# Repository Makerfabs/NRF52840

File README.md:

# MakePython nRF52840

```c++
/*
Version:		V2.0
Author:			UNKOWN
Create Date:	UNKOWN
Note:
	2020/7/24	v2.0: Rebuid readme,add pic. By Vincent
*/
```

[toc]

# Introduce

Python is one of the most widely used, simple and easy-to-learn programming languages around. CircuitPython is a lean implementation of the Python 3 programming language that has been pared down to run efficiently on microcontrollers.
MakePython nRF52840 is a powerful, generic BLE MCU module target to CircuitPython/MicroPython learners & developers. It is true “breadboard compatible”, with the very detailed pins explanation, it is easy to learn& use. The nRF52840 is ready to take advantage of the considerable performance improvements for Bluetooth Low Energy (LE) with the arrival of the Bluetooth 5 specification. Of greatest importance is the support for longer range (up to x4 compared to Bluetooth 4.x) and doubling of on-air data rate, up to 2 Mbs from 1 Mbs in Bluetooth 4.x
The MakePython nRF52840 leads out all pins of Nordic nRF52840, is programmed with CircuitPython by default, users can begin the CircuitPython developing as getting then on hand. It is also compatible with the Arduino making it easy to get started if the correct bootloader downloaded. There also the Makerfabs MakePython ESP8266, MakePython ESP32 and so on.

- You can get one from: [MakePython_nRF52840](https://www.makerfabs.com/makepython-nrf52840.html)

- Hardware and detailed instructions please visit Wiki page: [MakePython_nRF52840 Wiki](https://wiki.makerfabs.com/MaESP_nRF52840.html)

# Related Test

Visit the wiki for details.

- Display animation

- bluetooth communication

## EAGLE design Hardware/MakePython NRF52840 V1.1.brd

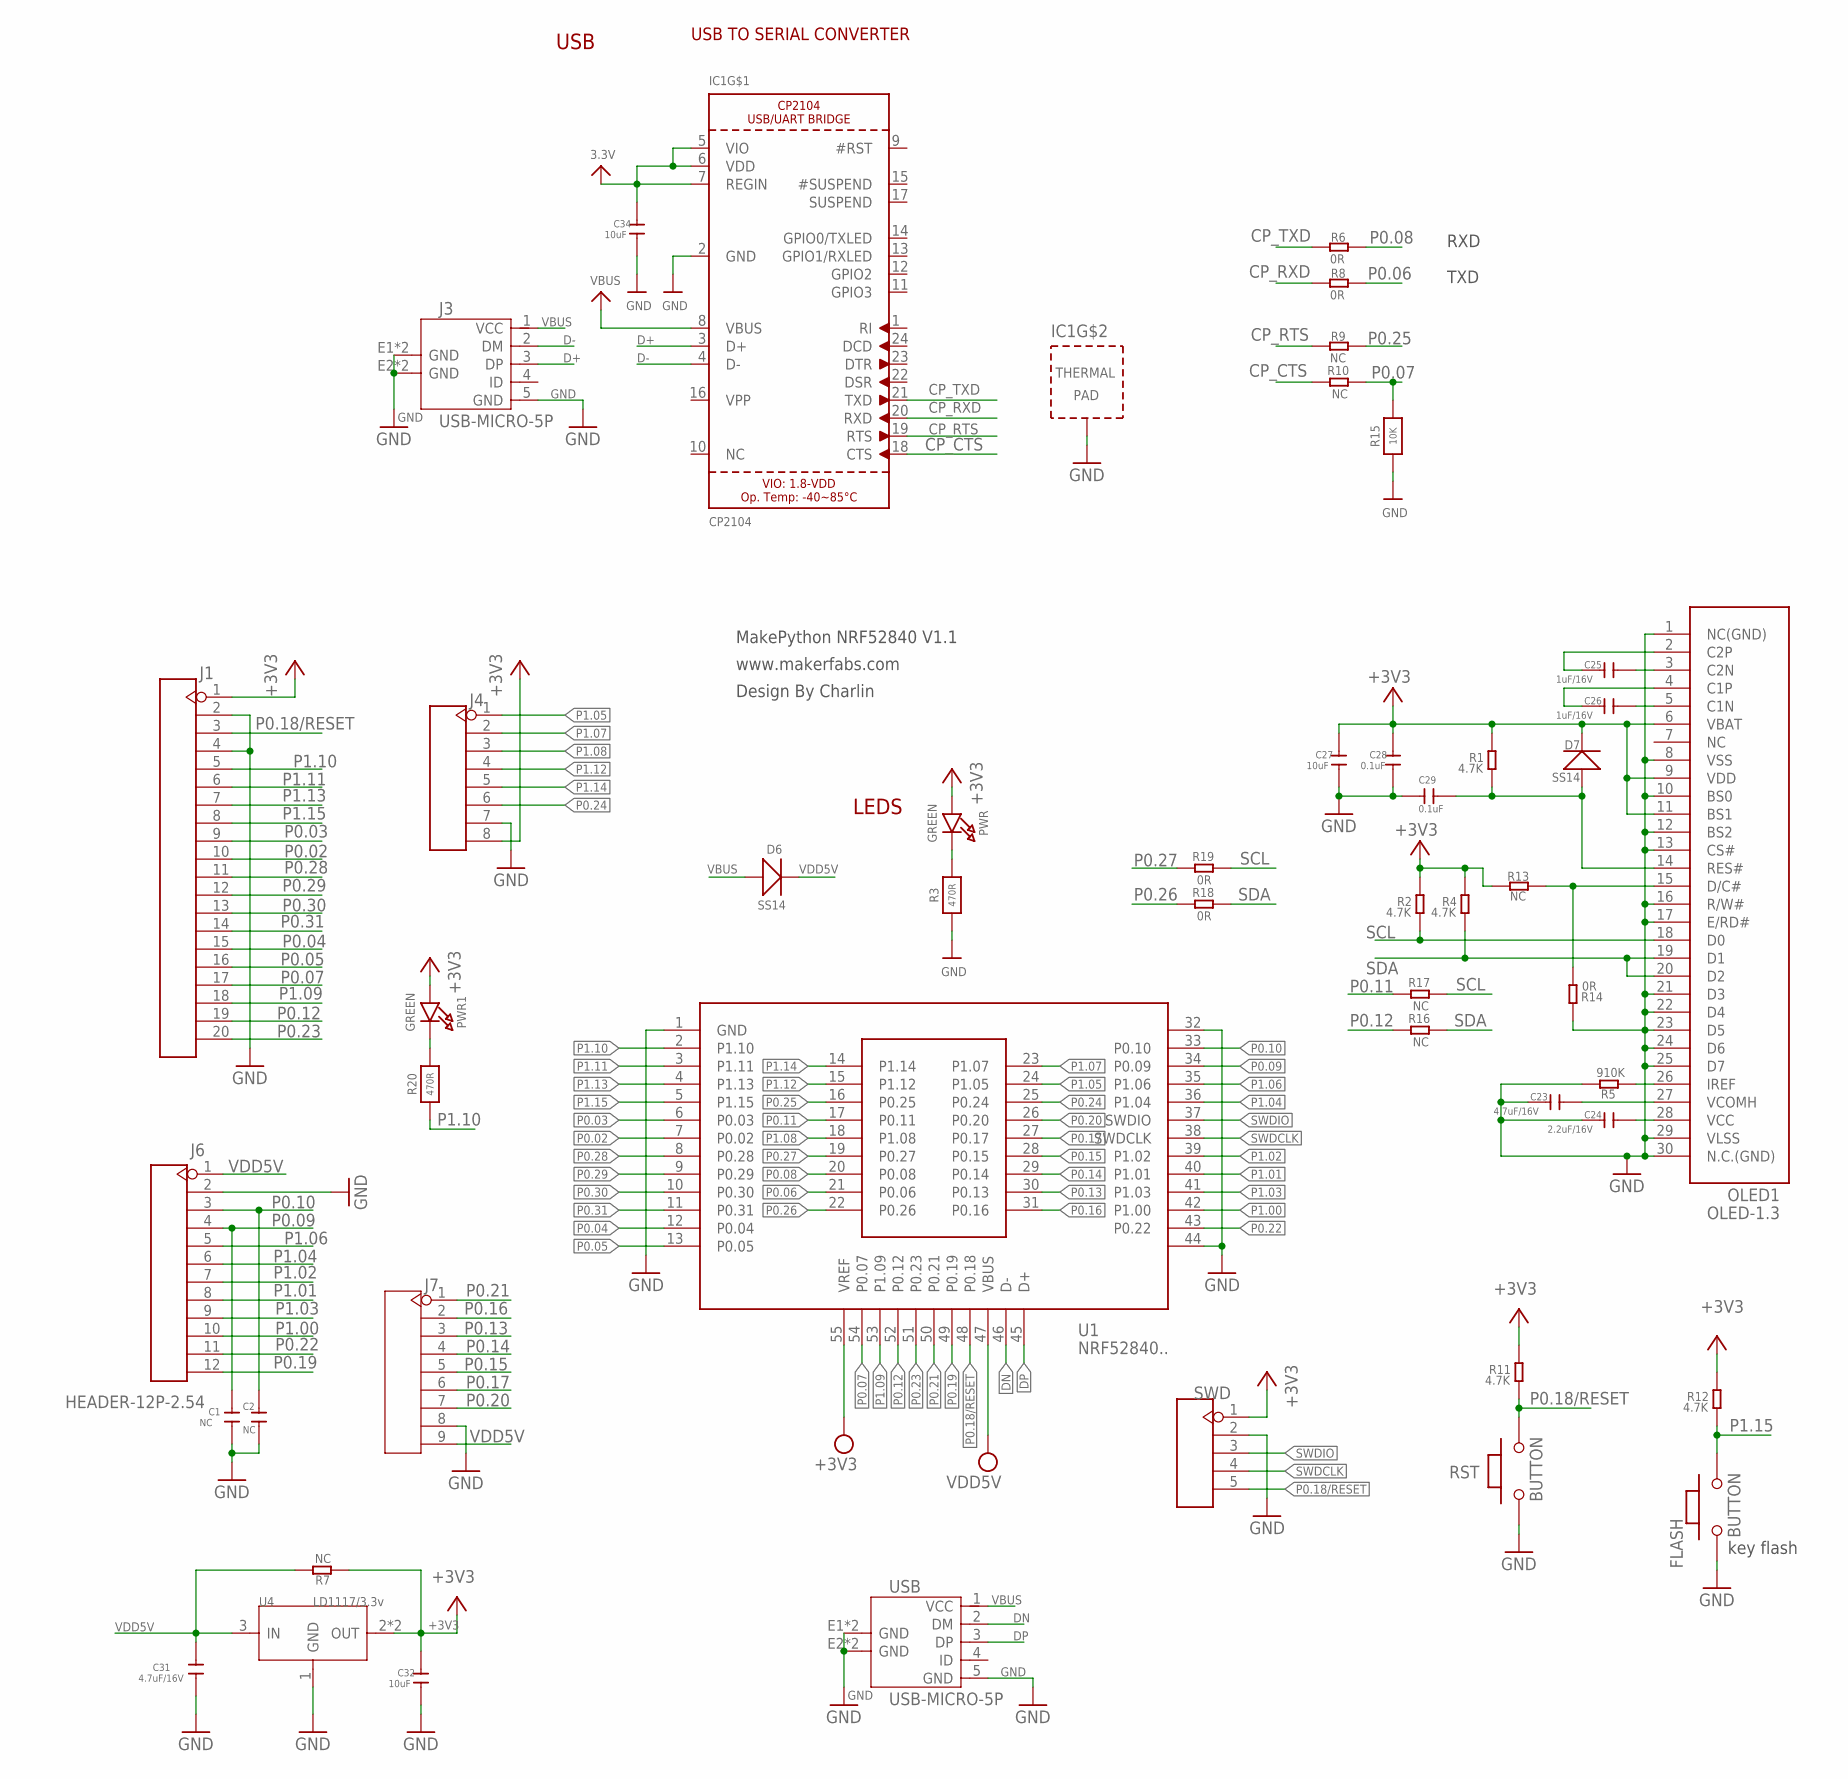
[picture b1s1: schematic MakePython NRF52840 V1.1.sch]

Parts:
C1, C2: NC; C0603
C23, C31: 4.7uF/16V; C0603
C24: 2.2uF/16V; C0603
C25, C26: 1uF/16V; C0603
C27, C32, C34: 10uF; C0603
C28, C29: 0.1uF; C0603
D6, D7: SS14; SOD323
FLASH: BUTTON; 157SW
IC1: CP2104; QFN24_4MM_SMSC
J1: HEADER-20P-2.54; 20P-2.54
J3: USB-MICRO-5P; MICRO-USB-5P
J4: HEADER-8P-2.54; 8P-2.54
J6: HEADER-12P-2.54; 12P-2.54
J7: HEADER-9P-2.54; 9P-2.54
OLED1: OLED-1.3
PWR, PWR1: GREEN; CHIPLED_0805_NOOUTLINE
R1, R2, R4, R11, R12: 4.7K; 0603
R3, R20: 470R; 0603-NO
R5: 910K; 0603
R6, R8, R14, R18, R19: 0R; 0603
R7, R9, R10, R13, R16, R17: NC; 0603
R15: 10K; 0603-NO
RST: BUTTON; 157SW
SWD: HEADER-5P-2.54; 5P-2.54
U1: NRF52840..
U4: LD1117/3.3v; SOT89
USB: USB-MICRO-5P; MICRO-USB-5P

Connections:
+3V3: C27.1, C28.1, C32.1, C34.1, D7.-, IC1.5 (VIO), IC1.6 (VDD), IC1.7 (REGIN), J1.1, J4.8, OLED1.6 (VBAT), OLED1.9 (VDD), OLED1.11 (BS1), PWR.A, PWR1.A, R1.2, R2.2, R4.2, R7.2, R11.2, R12.2, R13.2, SWD.1, U1.55 (VREF), U4.2 (OUT), U4.4 (OUT)
CP_CTS: IC1.18 (CTS), R10.2
CP_RTS: IC1.19 (RTS), R9.2
CP_RXD: IC1.20 (RXD), R8.2
CP_TXD: IC1.21 (TXD), R6.2
D+: IC1.3 (D+), J3.3 (DP)
D-: IC1.4 (D-), J3.2 (DM)
DN: U1.46 (D-), USB.2 (DM)
DP: U1.45 (D+), USB.3 (DP)
GND: C1.2, C2.2, C23.2, C24.2, C27.2, C28.2, C29.1, C31.2, C32.2, C34.2, FLASH.1, IC1.2 (GND), IC1.THERM (TP), J1.2, J1.4, J3.5 (GND), J3.E1 (GND), J3.E2 (GND), J3.P1 (GND), J3.P2 (GND), J4.7, J6.2, J7.8, OLED1.1 (NC(GND)), OLED1.8 (VSS), OLED1.10 (BS0), OLED1.12 (BS2), OLED1.13 (CS#), OLED1.16 (R/W#), OLED1.17 (E/RD#), OLED1.21 (D3), OLED1.22 (D4), OLED1.23 (D5), OLED1.24 (D6), OLED1.25 (D7), OLED1.29 (VLSS), OLED1.30 (N.C.(GND)), R3.1, R5.2, R14.2, R15.1, RST.1, SWD.2, U1.1 (GND), U1.32, U1.44, U4.1 (GND), USB.5 (GND), USB.E1 (GND), USB.E2 (GND), USB.P1 (GND), USB.P2 (GND)
unnamed: PWR1.C, R20.2
unnamed: OLED1.15 (D/C#), R13.1, R14.1
unnamed: PWR.C, R3.2
unnamed: C25.1, OLED1.3 (C2N)
unnamed: C25.2, OLED1.2 (C2P)
unnamed: C26.1, OLED1.5 (C1N)
unnamed: C26.2, OLED1.4 (C1P)
unnamed: C29.2, D7.+, OLED1.14 (RES#), R1.1
unnamed: OLED1.26 (IREF), R5.1
unnamed: C24.1, OLED1.28 (VCC)
unnamed: C23.1, OLED1.27 (VCOMH)
P0.02: J1.10, U1.7 (P0.02)
P0.03: J1.9, U1.6 (P0.03)
P0.04: J1.15, U1.12 (P0.04)
P0.05: J1.16, U1.13 (P0.05)
P0.06: R8.1, U1.21 (P0.06)
P0.07: J1.17, R10.1, R15.2, U1.54 (P0.07)
P0.08: R6.1, U1.20 (P0.08)
P0.09: C1.1, J6.4, U1.34 (P0.09)
P0.10: C2.1, J6.3, U1.33 (P0.10)
P0.11: R17.2, U1.17 (P0.11)
P0.12: J1.19, R16.2, U1.52 (P0.12)
P0.13: J7.3, U1.30 (P0.13)
P0.14: J7.4, U1.29 (P0.14)
P0.15: J7.5, U1.28 (P0.15)
P0.16: J7.2, U1.31 (P0.16)
P0.17: J7.6, U1.27 (P0.17)
P0.18/RESET: J1.3, R11.1, RST.2, SWD.5, U1.48 (P0.18)
P0.19: J6.12, U1.49 (P0.19)
P0.20: J7.7, U1.26 (P0.20)
P0.21: J7.1, U1.50 (P0.21)
P0.22: J6.11, U1.43 (P0.22)
P0.23: J1.20, U1.51 (P0.23)
P0.24: J4.6, U1.25 (P0.24)
P0.25: R9.1, U1.16 (P0.25)
P0.26: R18.2, U1.22 (P0.26)
P0.27: R19.2, U1.19 (P0.27)
P0.28: J1.11, U1.8 (P0.28)
P0.29: J1.12, U1.9 (P0.29)
P0.30: J1.13, U1.10 (P0.30)
P0.31: J1.14, U1.11 (P0.31)
P1.00: J6.10, U1.42 (P1.00)
P1.01: J6.8, U1.40 (P1.01)
P1.02: J6.7, U1.39 (P1.02)
P1.03: J6.9, U1.41 (P1.03)
P1.04: J6.6, U1.36 (P1.04)
P1.05: J4.1, U1.24 (P1.05)
P1.06: J6.5, U1.35 (P1.06)
P1.07: J4.2, U1.23 (P1.07)
P1.08: J4.3, U1.18 (P1.08)
P1.09: J1.18, U1.53 (P1.09)
P1.10: J1.5, R20.1, U1.2 (P1.10)
P1.11: J1.6, U1.3 (P1.11)
P1.12: J4.4, U1.15 (P1.12)
P1.13: J1.7, U1.4 (P1.13)
P1.14: J4.5, U1.14 (P1.14)
P1.15: FLASH.2, J1.8, R12.1, U1.5 (P1.15)
SCL: OLED1.18 (D0), R2.1, R17.1, R19.1
SDA: OLED1.19 (D1), OLED1.20 (D2), R4.1, R16.1, R18.1
SWDCLK: SWD.4, U1.38 (SWDCLK)
SWDIO: SWD.3, U1.37 (SWDIO)
VBUS: D6.+, IC1.8 (VBUS), J3.1 (VCC), USB.1 (VCC)
VDD5V: C31.1, D6.-, J6.1, J7.9, R7.1, U1.47 (VBUS), U4.3 (IN)

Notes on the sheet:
LEDS
key flash
USB
USB TO SERIAL CONVERTER
MakePython NRF52840 V1.1
www.makerfabs.com
Design By Charlin
RXD
TXD

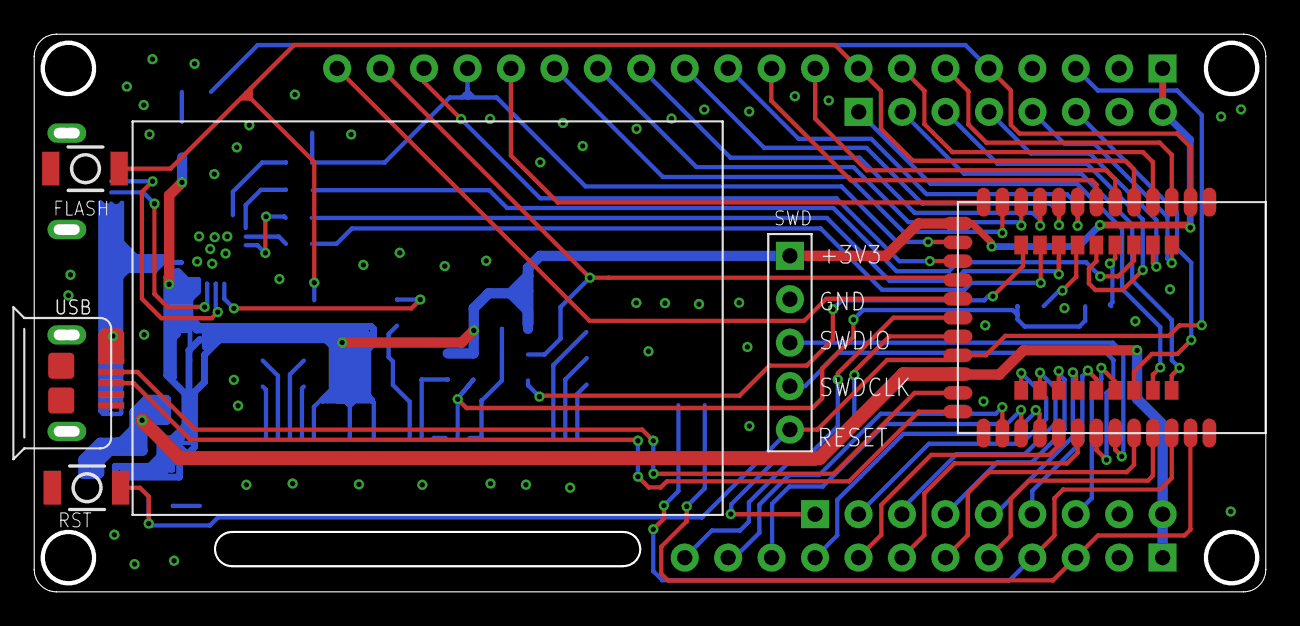
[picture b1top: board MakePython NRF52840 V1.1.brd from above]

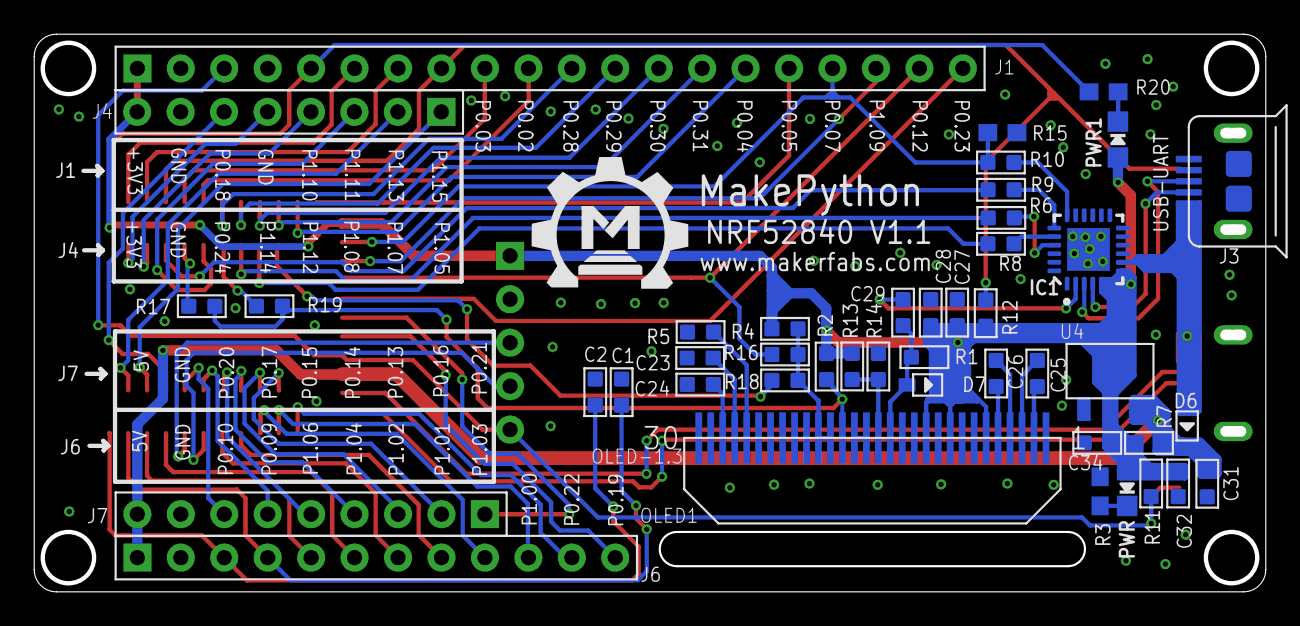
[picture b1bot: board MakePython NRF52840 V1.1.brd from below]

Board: 2 copper layers, 71.4 x 32.0 mm, 50 parts (44 on the bottom side), 73 nets.

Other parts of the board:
U$1: MAKERFABS_0.3

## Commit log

2020-04-29 Create Arduino
2020-04-30 Create tset
2020-04-30 Create README
2020-07-24 add pic
2021-11-03 add hardware

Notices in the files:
parts and their libraries:
microbuilder: This work is placed in the public domain, and may be freely used for commercial and non-commercial work with the following conditions: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
SparkFun-Aesthetics: Licensing: Creative Commons ShareAlike 4.0 International - https://creativecommons.org/licenses/by-sa/4.0
